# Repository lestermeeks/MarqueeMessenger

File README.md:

# MarqueeMessenger
Marquee Messenger Project Summary

# License
GPLv3

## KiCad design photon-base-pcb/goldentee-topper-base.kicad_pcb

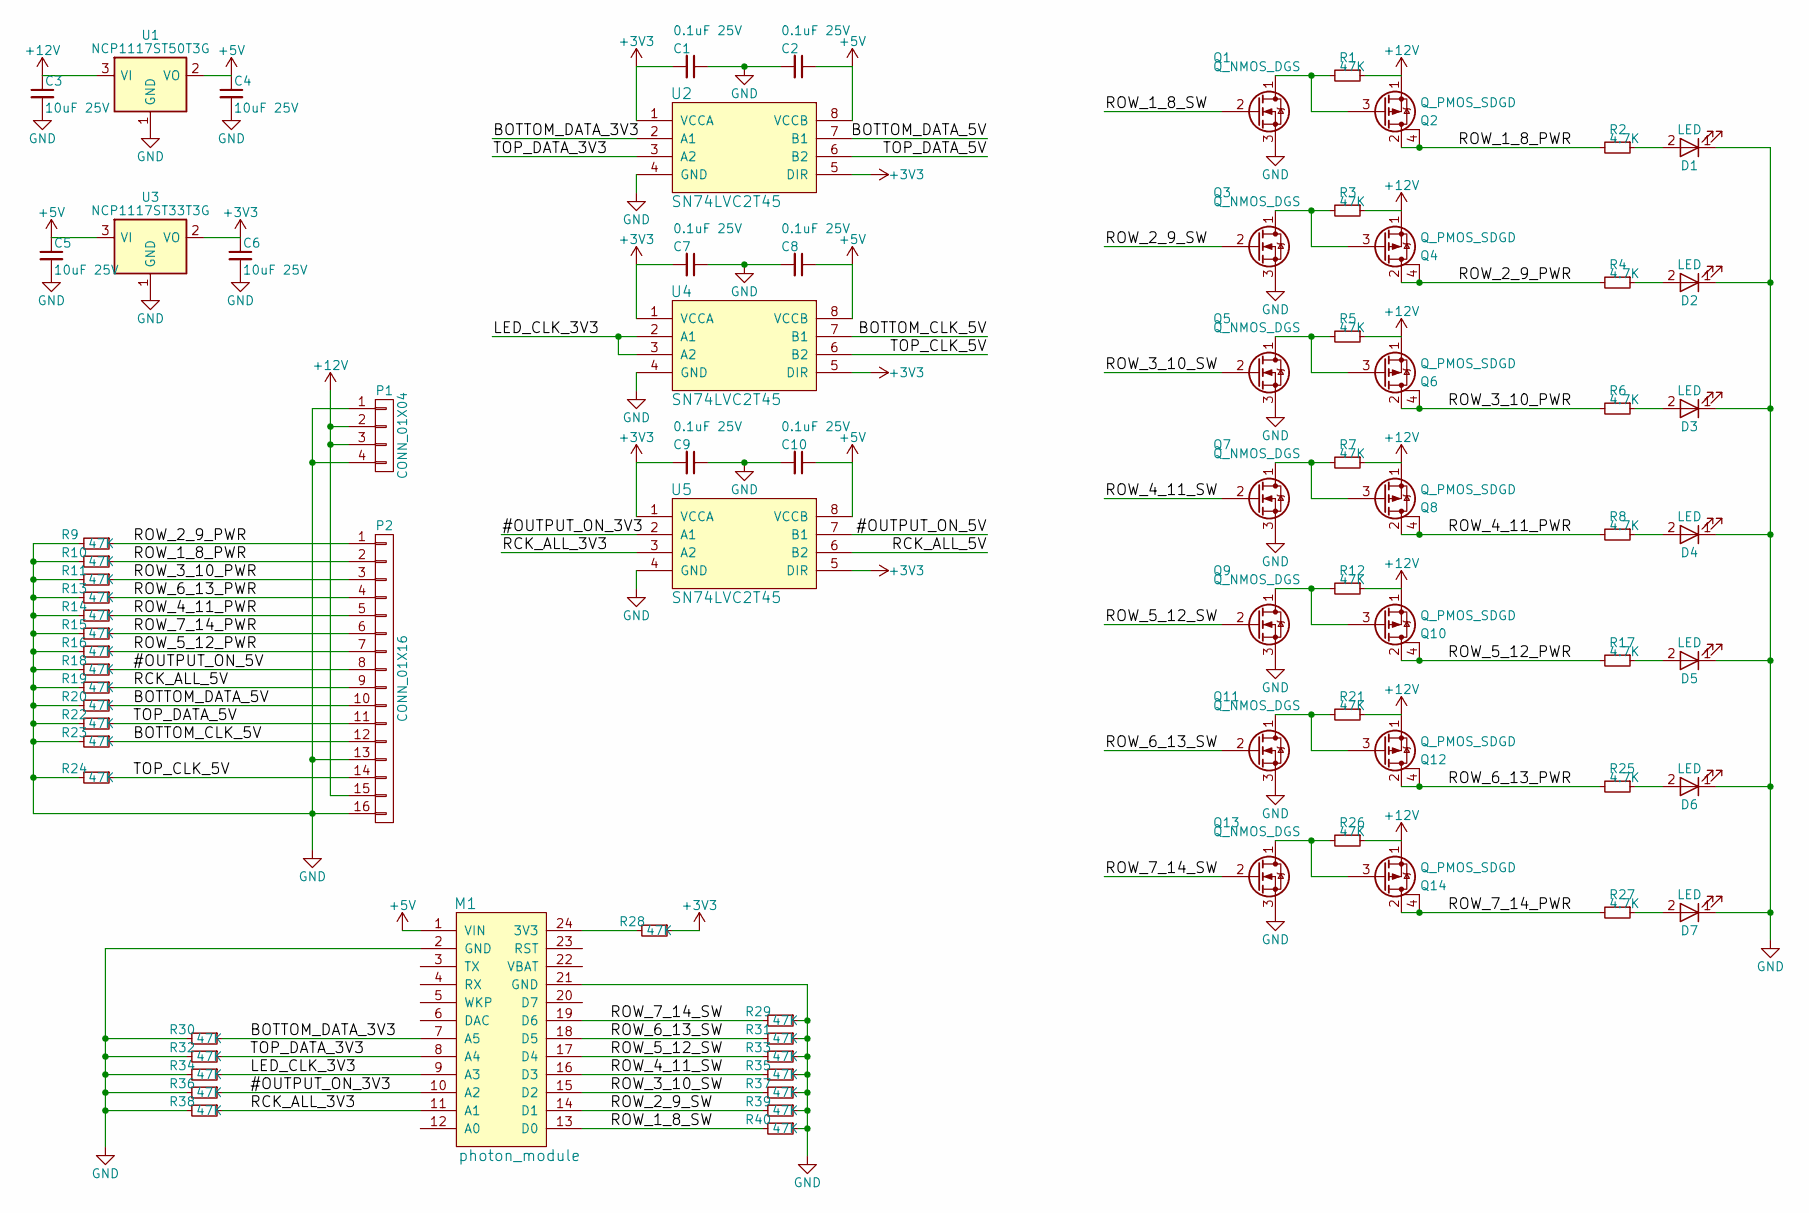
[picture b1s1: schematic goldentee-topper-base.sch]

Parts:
C1, C2, C7, C8, C9, C10: 0.1uF 25V; C_0805_HandSoldering
C3, C4, C5, C6: 10uF 25V; C_1210_HandSoldering
D1, D2, D3, D4, D5, D6, D7: LED; LED_0603
M1: photon_module; photon
P1: CONN_01X04; CONN_0.156
P2: CONN_01X16; CONN_1x16_0.156
Q1, Q3, Q5, Q7, Q9, Q11, Q13: Q_NMOS_DGS; SOT-23_Handsoldering
Q2, Q4, Q6, Q8, Q10, Q12, Q14: Q_PMOS_SDGD; SOT-223
R1, R3, R5, R7, R9, R10, R11, R12, R13, R14, R15, R16, R18, R19, R20, R21, R22, R23, R24, R26, R28, R29, R30, R31, R32, R33, R34, R35, R36, R37, R38, R39, R40: 47K; R_0603_HandSoldering
R2, R4, R6, R8, R17, R25, R27: 4.7K; R_0603_HandSoldering
U1: NCP1117ST50T3G; SOT-223
U2, U4, U5: SN74LVC2T45; SOIC-8-N
U3: NCP1117ST33T3G; SOT-223

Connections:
+3V3: C1.2, C6.1, C7.2, C9.2, R28.1, U2.1 (VCCA), U2.5 (DIR), U3.2 (VO), U4.1 (VCCA), U4.5 (DIR), U5.1 (VCCA), U5.5 (DIR)
+5V: C2.1, C4.1, C5.1, C8.1, C10.1, M1.1 (VIN), U1.2 (VO), U2.8 (VCCB), U3.3 (VI), U4.8 (VCCB), U5.8 (VCCB)
+12V: C3.1, P1.2, P1.3, P2.15, Q2.1 (S), Q4.1 (S), Q6.1 (S), Q8.1 (S), Q10.1 (S), Q12.1 (S), Q14.1 (S), R1.1, R3.1, R5.1, R7.1, R12.1, R21.1, R26.1, U1.3 (VI)
/#OUTPUT_ON_3V3: M1.10 (A2), R36.1, U5.2 (A1)
/#OUTPUT_ON_5V: P2.8, R18.1, U5.7 (B1)
/BOTTOM_CLK_5V: P2.12, R23.1, U4.7 (B1)
/BOTTOM_DATA_3V3: M1.7 (A5), R30.1, U2.2 (A1)
/BOTTOM_DATA_5V: P2.10, R20.1, U2.7 (B1)
/LED_CLK_3V3: M1.9 (A3), R34.1, U4.2 (A1), U4.3 (A2)
/RCK_ALL_3V3: M1.11 (A1), R38.1, U5.3 (A2)
/RCK_ALL_5V: P2.9, R19.1, U5.6 (B2)
/ROW_1_8_PWR: P2.2, Q2.2 (D), Q2.4 (D), R2.2, R10.1
/ROW_1_8_SW: M1.13 (D0), Q1.2 (G), R40.2
/ROW_2_9_PWR: P2.1, Q4.2 (D), Q4.4 (D), R4.2, R9.1
/ROW_2_9_SW: M1.14 (D1), Q3.2 (G), R39.2
/ROW_3_10_PWR: P2.3, Q6.2 (D), Q6.4 (D), R6.2, R11.1
/ROW_3_10_SW: M1.15 (D2), Q5.2 (G), R37.2
/ROW_4_11_PWR: P2.5, Q8.2 (D), Q8.4 (D), R8.2, R14.1
/ROW_4_11_SW: M1.16 (D3), Q7.2 (G), R35.2
/ROW_5_12_PWR: P2.7, Q10.2 (D), Q10.4 (D), R16.1, R17.2
/ROW_5_12_SW: M1.17 (D4), Q9.2 (G), R33.2
/ROW_6_13_PWR: P2.4, Q12.2 (D), Q12.4 (D), R13.1, R25.2
/ROW_6_13_SW: M1.18 (D5), Q11.2 (G), R31.2
/ROW_7_14_PWR: P2.6, Q14.2 (D), Q14.4 (D), R15.1, R27.2
/ROW_7_14_SW: M1.19 (D6), Q13.2 (G), R29.2
/TOP_CLK_5V: P2.14, R24.1, U4.6 (B2)
/TOP_DATA_3V3: M1.8 (A4), R32.1, U2.3 (A2)
/TOP_DATA_5V: P2.11, R22.1, U2.6 (B2)
GND: C1.1, C2.2, C3.2, C4.2, C5.2, C6.2, C7.1, C8.2, C9.1, C10.2, D1.1 (K), D2.1 (K), D3.1 (K), D4.1 (K), D5.1 (K), D6.1 (K), D7.1 (K), M1.2 (GND), M1.21 (GND), P1.1, P1.4, P2.13, P2.16, Q1.3 (S), Q3.3 (S), Q5.3 (S), Q7.3 (S), Q9.3 (S), Q11.3 (S), Q13.3 (S), R9.2, R10.2, R11.2, R13.2, R14.2, R15.2, R16.2, R18.2, R19.2, R20.2, R22.2, R23.2, R24.2, R29.1, R30.2, R31.1, R32.2, R33.1, R34.2, R35.1, R36.2, R37.1, R38.2, R39.1, R40.1, U1.1 (GND), U2.4 (GND), U3.1 (GND), U4.4 (GND), U5.4 (GND)
unnamed: D1.2 (A), R2.1
unnamed: D2.2 (A), R4.1
unnamed: D3.2 (A), R6.1
unnamed: D4.2 (A), R8.1
unnamed: D5.2 (A), R17.1
unnamed: D6.2 (A), R25.1
unnamed: D7.2 (A), R27.1
unnamed: M1.24 (3V3), R28.2
unnamed: Q1.1 (D), Q2.3 (G), R1.2
unnamed: Q3.1 (D), Q4.3 (G), R3.2
unnamed: Q5.1 (D), Q6.3 (G), R5.2
unnamed: Q7.1 (D), Q8.3 (G), R7.2
unnamed: Q9.1 (D), Q10.3 (G), R12.2
unnamed: Q11.1 (D), Q12.3 (G), R21.2
unnamed: Q13.1 (D), Q14.3 (G), R26.2

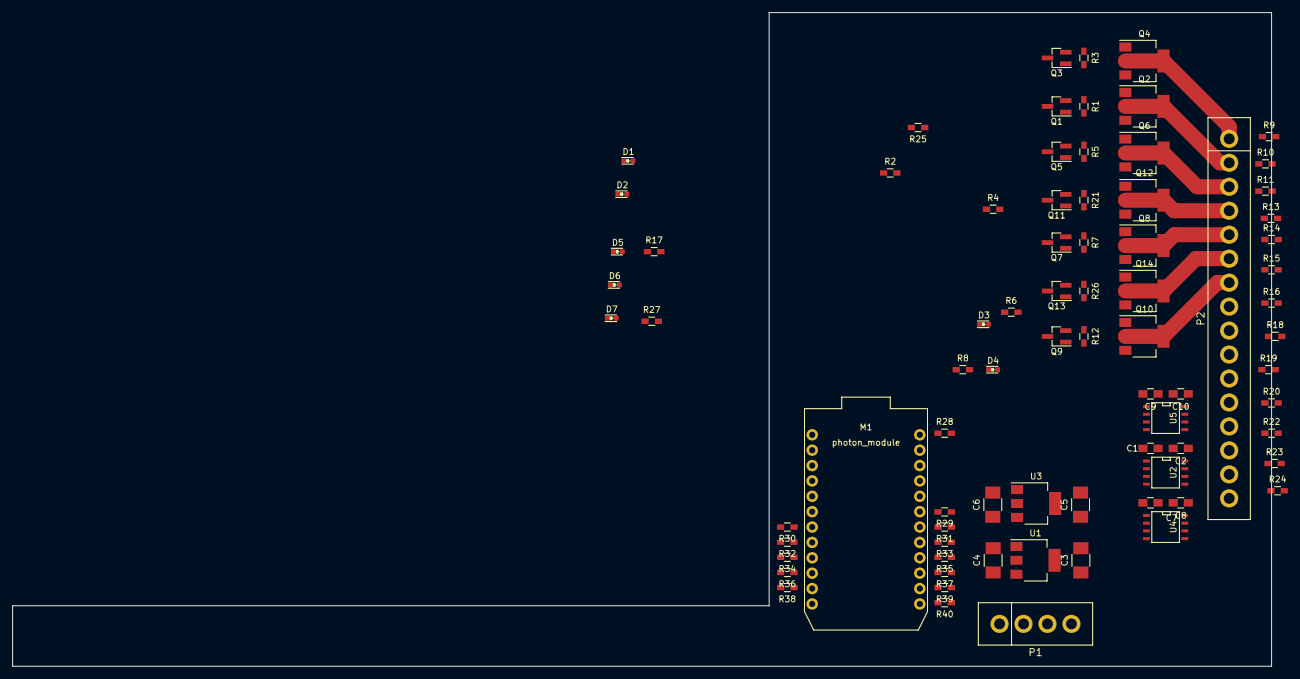
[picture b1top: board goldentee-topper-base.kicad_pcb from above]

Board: 2 copper layers, 208.0 x 108.0 mm, 79 parts (0 on the bottom side), 44 nets.

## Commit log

2021-02-11 prototype fab zips
